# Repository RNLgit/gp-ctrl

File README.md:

# gp-ctrl
general purpose control board

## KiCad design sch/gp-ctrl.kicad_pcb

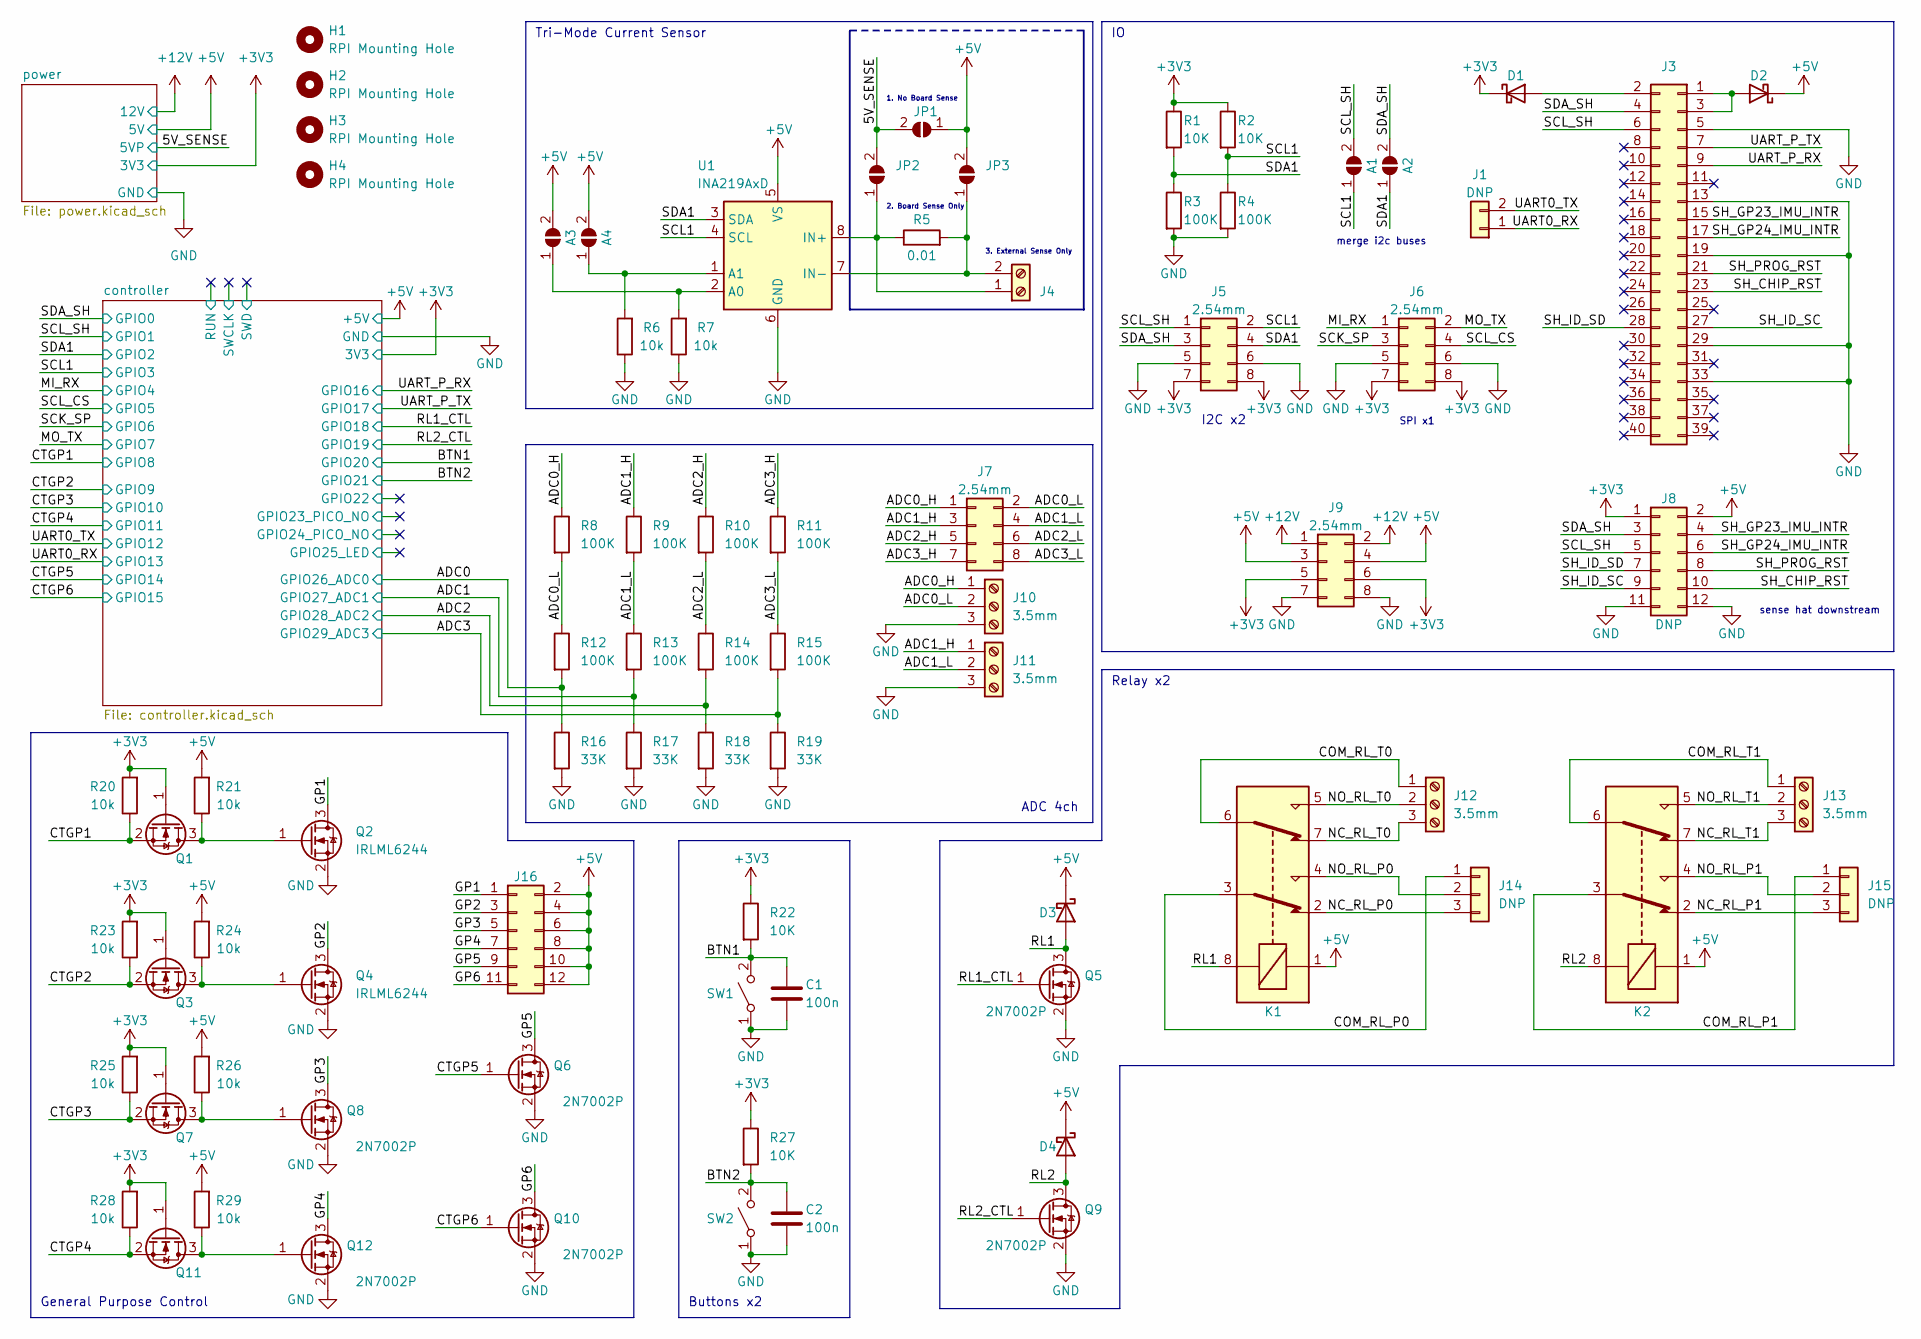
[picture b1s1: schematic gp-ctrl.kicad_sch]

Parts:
A1, A2, A3, A4: SolderJumper_2_Open; SolderJumper-2_P1.3mm_Open_TrianglePad1.0x1.5mm
C1, C2: 100n; R_0402_1005Metric_Pad0.72x0.64mm_HandSolder; LCSC C1525
D1, D2: SS34; D_SMA; LCSC C8678
D3, D4: B5819W SL; D_SOD-123; LCSC C8598
H1, H2, H3, H4: RPI Mounting Hole; MountingHole_3.2mm_M3_Pad
J1: DNP; PinHeader_1x02_P2.54mm_Vertical
J3: Conn_02x20_Odd_Even; Samtec_HLE-120-02-xxx-DV-BE_2x20_P2.54mm_Horizontal; LCSC C3975165
J4: Screw_Terminal_3.5mm; TerminalBlock_4Ucon_1x02_P3.50mm_Horizontal; LCSC C466970
J5, J6, J7, J9: 2.54mm; PinHeader_2x04_P2.54mm_Vertical; LCSC C225519
J8: DNP; PinHeader_2x06_P2.54mm_Vertical
J10, J11, J12, J13: 3.5mm; TerminalBlock_4Ucon_1x03_P3.50mm_Horizontal; LCSC C695630
J14, J15: DNP; PinHeader_1x03_P2.54mm_Vertical_SMD_Pin1Left
J16: Conn_02x06_Odd_Even; PinHeader_2x06_P2.54mm_Vertical; LCSC C225521
JP1, JP2, JP3: SolderJumper_2_Open; power_jumper
K1, K2: Relay_DPDT_Panasonic_AGQ200A4H; LCSC C490150
Q1, Q3, Q5, Q6, Q7, Q8, Q9, Q10, Q11, Q12: 2N7002P; SOT-23; LCSC C8545
Q2, Q4: IRLML6244; SOT-23; LCSC C143946
R1, R2, R22, R27: 10K; R_0603_1608Metric_Pad0.98x0.95mm_HandSolder; LCSC C25804
R3, R4, R8, R9, R10, R11, R12, R13, R14, R15: 100K; R_0603_1608Metric_Pad0.98x0.95mm_HandSolder; LCSC C25803
R5: 0.01; R_1210_3225Metric_Pad1.30x2.65mm_HandSolder; LCSC C473495
R6, R7, R20, R21, R23, R24, R25, R26, R28, R29: 10k; R_0402_1005Metric_Pad0.72x0.64mm_HandSolder; LCSC C25086
R16, R17, R18, R19: 33K; R_0603_1608Metric_Pad0.98x0.95mm_HandSolder; LCSC C4216
SW1, SW2: C2689642; SW_SPST_CK_PTS636_SP43_SMTR; LCSC C2689642
U1: INA219AxD; SOIC-8_3.9x4.9mm_P1.27mm; LCSC C138706

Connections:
+3V3: D1.1 (K), J5.7, J5.8, J6.7, J6.8, J8.1, J9.5, J9.6, Q1.1 (G), Q3.1 (G), Q7.1 (G), Q11.1 (G), R1.1, R2.1, R20.2, R22.1, R23.2, R25.2, R27.1, R28.2; also elsewhere on the board
+5V: A3.2 (B), A4.2 (B), D2.1 (K), D3.1 (K), D4.1 (K), J8.2, J9.3, J9.4, J16.2, J16.4, J16.6, J16.8, J16.10, J16.12, JP1.1 (A), JP3.2 (B), K1.1, K2.1, R21.2, R24.2, R26.2, R29.2, U1.5 (VS); also elsewhere on the board
+5VP: JP1.2 (B), JP2.2 (B); also elsewhere on the board
+12V: J9.1, J9.2; also elsewhere on the board
/ADC0: R12.2, R16.1; also elsewhere on the board
/ADC0_H: J7.1, J10.1, R8.1
/ADC0_L: J7.2, J10.2, R8.2, R12.1
/ADC1: R13.2, R17.1; also elsewhere on the board
/ADC1_H: J7.3, J11.1, R9.1
/ADC1_L: J7.4, J11.2, R9.2, R13.1
/ADC2: R14.2, R18.1; also elsewhere on the board
/ADC2_H: J7.5, R10.1
/ADC2_L: J7.6, R10.2, R14.1
/ADC3: R15.2, R19.1; also elsewhere on the board
/ADC3_H: J7.7, R11.1
/ADC3_L: J7.8, R11.2, R15.1
/BTN1: C1.1, R22.2, SW1.2 (B); also elsewhere on the board
/BTN2: C2.1, R27.2, SW2.2 (B); also elsewhere on the board
/COM_RL_P0: J14.1, K1.3
/COM_RL_P1: J15.1, K2.3
/COM_RL_T0: J12.1, K1.6
/COM_RL_T1: J13.1, K2.6
/CTGP1: Q1.2 (S), R20.1; also elsewhere on the board
/CTGP2: Q3.2 (S), R23.1; also elsewhere on the board
/CTGP3: Q7.2 (S), R25.1; also elsewhere on the board
/CTGP4: Q11.2 (S), R28.1; also elsewhere on the board
/CTGP5: Q6.1 (G); also elsewhere on the board
/CTGP6: Q10.1 (G); also elsewhere on the board
/GP1: J16.1, Q2.3 (D)
/GP2: J16.3, Q4.3 (D)
/GP3: J16.5, Q8.3 (D)
/GP4: J16.7, Q12.3 (D)
/GP5: J16.9, Q6.3 (D)
/GP6: J16.11, Q10.3 (D)
/MI_RX: J6.1; also elsewhere on the board
/MO_TX: J6.2; also elsewhere on the board
/NC_RL_P0: J14.3, K1.2
/NC_RL_P1: J15.3, K2.2
/NC_RL_T0: J12.3, K1.7
/NC_RL_T1: J13.3, K2.7
/NO_RL_P0: J14.2, K1.4
/NO_RL_P1: J15.2, K2.4
/NO_RL_T0: J12.2, K1.5
/NO_RL_T1: J13.2, K2.5
/RL1: D3.2 (A), K1.8, Q5.3 (D)
/RL1_CTL: Q5.1 (G); also elsewhere on the board
/RL2: D4.2 (A), K2.8, Q9.3 (D)
/RL2_CTL: Q9.1 (G); also elsewhere on the board
/SCK_SP: J6.3; also elsewhere on the board
/SCL1: A1.1 (A), J5.2, R2.2, R4.1, U1.4 (SCL); also elsewhere on the board
/SCL_CS: J6.4; also elsewhere on the board
/SCL_SH: A1.2 (B), J3.6, J5.1, J8.5; also elsewhere on the board
/SDA1: A2.1 (A), J5.4, R1.2, R3.1, U1.3 (SDA); also elsewhere on the board
/SDA_SH: A2.2 (B), J3.4, J5.3, J8.3; also elsewhere on the board
/SH_CHIP_RST: J3.23, J8.10
/SH_GP23_IMU_INTR: J3.15, J8.4
/SH_GP24_IMU_INTR: J3.17, J8.6
/SH_ID_SC: J3.27, J8.9
/SH_ID_SD: J3.28, J8.7
/SH_PROG_RST: J3.21, J8.8
/UART0_RX: J1.1; also elsewhere on the board
/UART0_TX: J1.2; also elsewhere on the board
/UART_P_RX: J3.9; also elsewhere on the board
/UART_P_TX: J3.7; also elsewhere on the board
GND: C1.2, C2.2, J3.5, J3.13, J3.19, J3.29, J3.33, J5.5, J5.6, J6.5, J6.6, J8.11, J8.12, J9.7, J9.8, J10.3, J11.3, Q2.2 (S), Q4.2 (S), Q5.2 (S), Q6.2 (S), Q8.2 (S), Q9.2 (S), Q10.2 (S), Q12.2 (S), R3.2, R4.2, R6.1, R7.1, R16.2, R17.2, R18.2, R19.2, SW1.1 (A), SW2.1 (A), U1.6 (GND); also elsewhere on the board
unnamed: A3.1 (A), R7.2, U1.2 (A0)
unnamed: A4.1 (A), R6.2, U1.1 (A1)
unnamed: D2.2 (A), J3.1, J3.3
unnamed: D1.2 (A), J3.2
unnamed: J4.1, JP2.1 (A), R5.1, U1.8 (IN+)
unnamed: J4.2, JP3.1 (A), R5.2, U1.7 (IN-)
unnamed: Q1.3 (D), Q2.1 (G), R21.1
unnamed: Q3.3 (D), Q4.1 (G), R24.1
unnamed: Q7.3 (D), Q8.1 (G), R26.1
unnamed: Q11.3 (D), Q12.1 (G), R29.1

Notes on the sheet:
Buttons x2
3. External Sense Only
2. Board Sense Only
General Purpose Control
SPI x1
ADC 4ch
sense hat downstream
Relay x2
merge i2c buses
Tri-Mode Current Sensor
1. No Board Sense
I2C x2

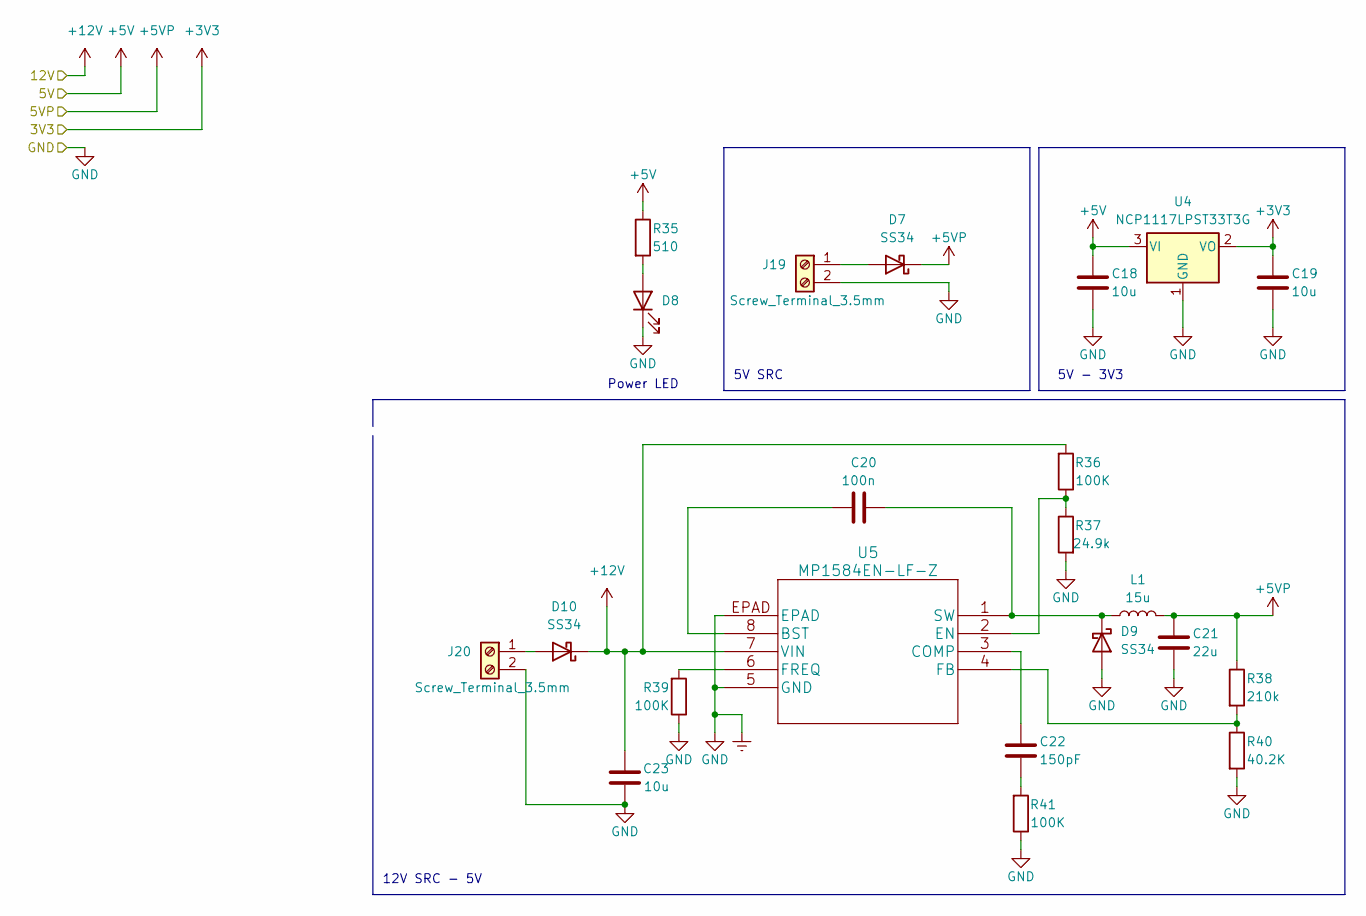
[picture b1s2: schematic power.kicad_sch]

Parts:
C18, C19: 10u; C_0603_1608Metric_Pad1.08x0.95mm_HandSolder; LCSC C96446
C20: 100n; R_0402_1005Metric_Pad0.72x0.64mm_HandSolder; LCSC C1525
C21: 22u; C_1206_3216Metric_Pad1.33x1.80mm_HandSolder; LCSC C12891
C22: 150pF; R_0402_1005Metric_Pad0.72x0.64mm_HandSolder; LCSC C1527
C23: 10u; C_0805_2012Metric_Pad1.18x1.45mm_HandSolder; LCSC C440198
D7, D9, D10: SS34; D_SMA; LCSC C8678
D8: 19-217/GHC-YR1S2/3T; D_0603_1608Metric_Pad1.05x0.95mm_HandSolder; LCSC C72043
J19, J20: Screw_Terminal_3.5mm; TerminalBlock_4Ucon_1x02_P3.50mm_Horizontal; LCSC C466970
L1: 15u; L_12x12mm_H6mm; LCSC C169384
R35: 510; R_0402_1005Metric_Pad0.72x0.64mm_HandSolder; LCSC C25123
R36, R39, R41: 100K; R_0402_1005Metric_Pad0.72x0.64mm_HandSolder; LCSC C25741
R37: 24.9k; R_0402_1005Metric_Pad0.72x0.64mm_HandSolder; LCSC C226371
R38: 210k; R_0402_1005Metric_Pad0.72x0.64mm_HandSolder; LCSC C58827
R40: 40.2K; R_0402_1005Metric_Pad0.72x0.64mm_HandSolder; LCSC C137983
U4: NCP1117LPST33T3G; SOT-223-3_TabPin2; LCSC C146799
U5: MP1584EN-LF-Z; LCSC C15051

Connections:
+3V3: C19.1, U4.2 (VO); also elsewhere on the board
+5V: C18.1, R35.1, U4.3 (VI); also elsewhere on the board
+5VP: C21.1, D7.1 (K), L1.2, R38.1; also elsewhere on the board
+12V: C23.1, D10.1 (K), R36.2, U5.7 (VIN); also elsewhere on the board
GND: C18.2, C19.2, C21.2, C23.2, D8.1 (K), D9.2 (A), J19.2, J20.2, R37.2, R39.1, R40.2, R41.1, U4.1 (GND), U5.5 (GND), U5.EPAD; also elsewhere on the board
unnamed: C20.1, D9.1 (K), L1.1, U5.1 (SW)
unnamed: C20.2, U5.8 (BST)
unnamed: C22.1, U5.3 (COMP)
unnamed: C22.2, R41.2
unnamed: D7.2 (A), J19.1
unnamed: D8.2 (A), R35.2
unnamed: D10.2 (A), J20.1
unnamed: R36.1, R37.1, U5.2 (EN)
unnamed: R38.2, R40.1, U5.4 (FB)
unnamed: R39.2, U5.6 (FREQ)

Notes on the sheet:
5V - 3V3
12V SRC - 5V
Power LED
5V SRC

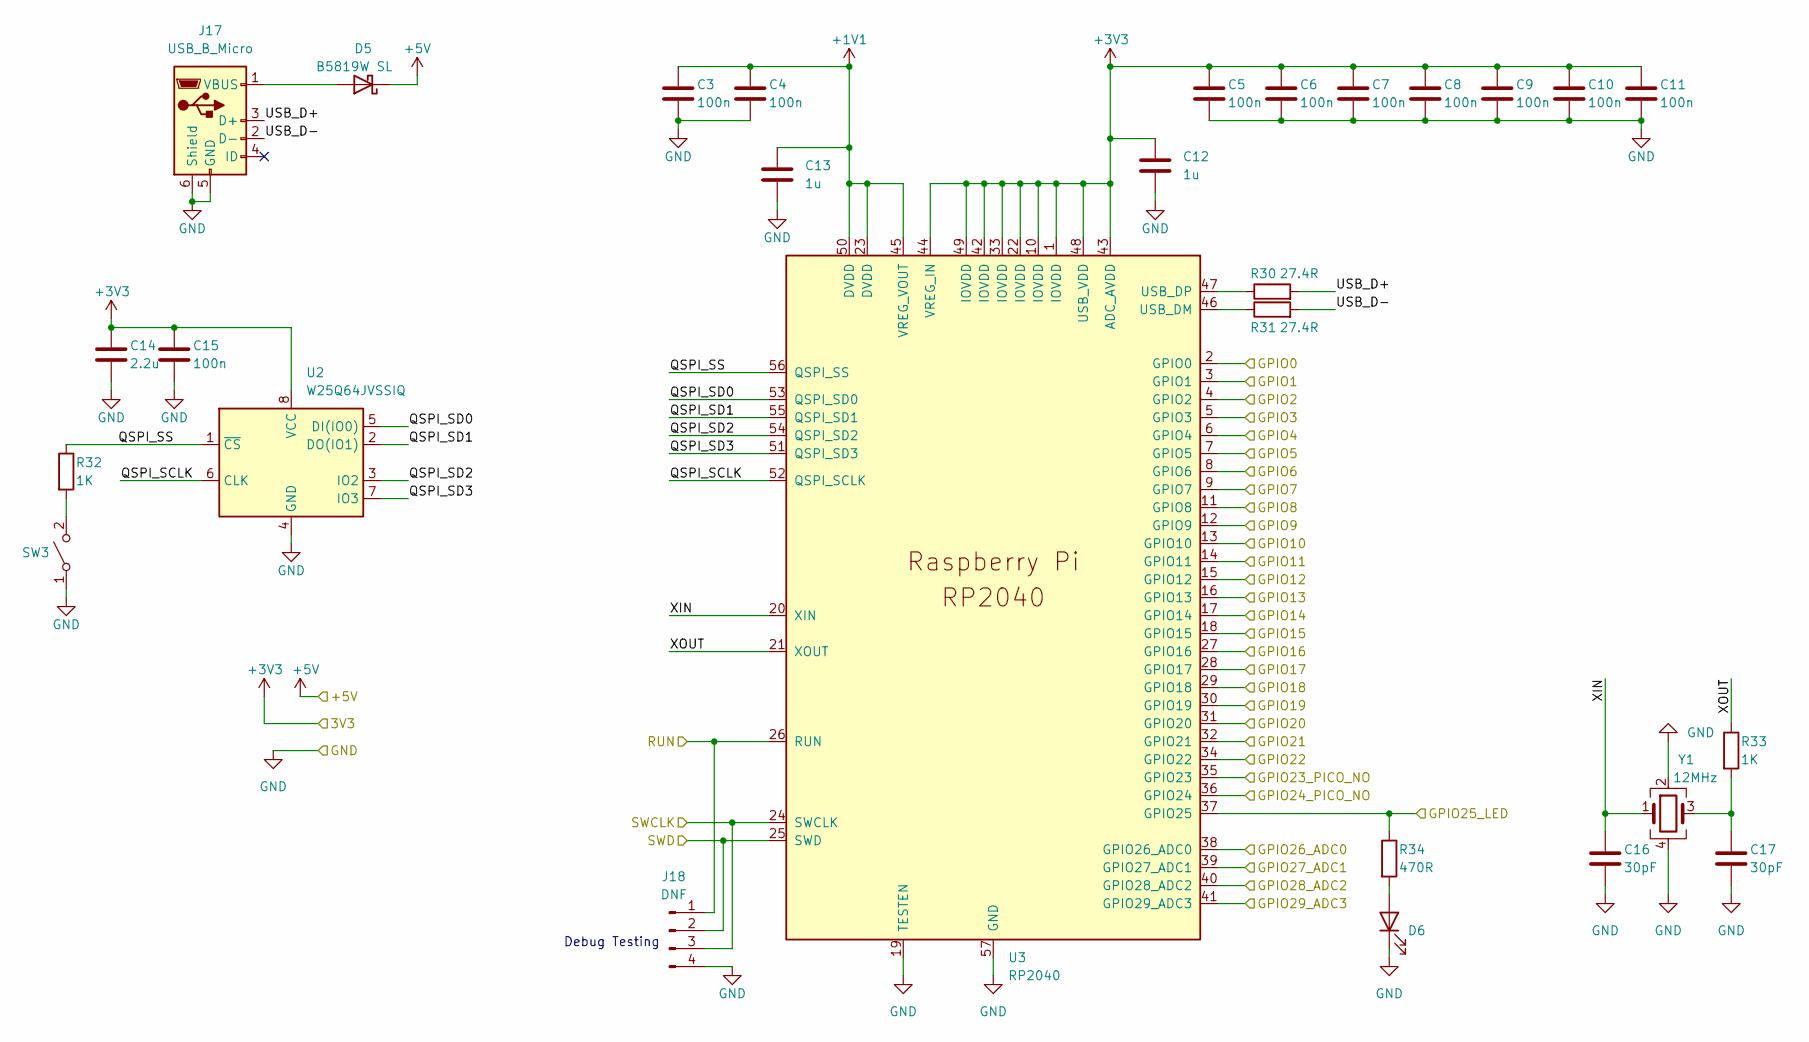
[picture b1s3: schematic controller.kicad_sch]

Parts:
C3, C4, C5, C6, C7, C8, C9, C10, C11: 100n; R_0402_1005Metric_Pad0.72x0.64mm_HandSolder; LCSC C1525
C12, C13: 1u; R_0402_1005Metric_Pad0.72x0.64mm_HandSolder; LCSC C52923
C14: 2.2u; L_0402_1005Metric_Pad0.77x0.64mm_HandSolder; LCSC C12530
C15: 100n; L_0402_1005Metric_Pad0.77x0.64mm_HandSolder; LCSC C1525
C16, C17: 30pF; C_0402_1005Metric_Pad0.74x0.62mm_HandSolder; LCSC C1570
D5: B5819W SL; D_SOD-123; LCSC C8598
D6: 19-217/GHC-YR1S2/3T; D_0603_1608Metric_Pad1.05x0.95mm_HandSolder; LCSC C72043
J17: USB_B_Micro; USB_Micro-B_Molex-105017-0001; LCSC C10418
J18: DNF; PinHeader_1x04_P1.00mm_Vertical_SMD_Pin1Left
R30, R31: 27.4R; R_0402_1005Metric_Pad0.72x0.64mm_HandSolder; LCSC C31439
R32, R33: 1K; L_0402_1005Metric_Pad0.77x0.64mm_HandSolder; LCSC C11702
R34: 470R; R_0402_1005Metric_Pad0.72x0.64mm_HandSolder; LCSC C25117
SW3: C2689642; SW_SPST_CK_PTS636_SP43_SMTR; LCSC C2689642
U2: W25Q64JVSSIQ; SOIC-8_5.23x5.23mm_P1.27mm; LCSC C83140
U3: RP2040; RP2040-QFN-56; LCSC C2040
Y1: 12MHz; Crystal_SMD_3225-4Pin_3.2x2.5mm; LCSC C9002

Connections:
+1V1: C3.1, C4.1, C13.1, U3.23 (DVDD), U3.45 (VREG_VOUT), U3.50 (DVDD)
+3V3: C5.1, C6.1, C7.1, C8.1, C9.1, C10.1, C11.1, C12.1, C14.1, C15.1, U2.8 (VCC), U3.1 (IOVDD), U3.10 (IOVDD), U3.22 (IOVDD), U3.33 (IOVDD), U3.42 (IOVDD), U3.43 (ADC_AVDD), U3.44 (VREG_IN), U3.48 (USB_VDD), U3.49 (IOVDD); also elsewhere on the board
+5V: D5.1 (K); also elsewhere on the board
/ADC0: U3.38 (GPIO26_ADC0); also elsewhere on the board
/ADC1: U3.39 (GPIO27_ADC1); also elsewhere on the board
/ADC2: U3.40 (GPIO28_ADC2); also elsewhere on the board
/ADC3: U3.41 (GPIO29_ADC3); also elsewhere on the board
/BTN1: U3.31 (GPIO20); also elsewhere on the board
/BTN2: U3.32 (GPIO21); also elsewhere on the board
/CTGP1: U3.11 (GPIO8); also elsewhere on the board
/CTGP2: U3.12 (GPIO9); also elsewhere on the board
/CTGP3: U3.13 (GPIO10); also elsewhere on the board
/CTGP4: U3.14 (GPIO11); also elsewhere on the board
/CTGP5: U3.17 (GPIO14); also elsewhere on the board
/CTGP6: U3.18 (GPIO15); also elsewhere on the board
/MI_RX: U3.6 (GPIO4); also elsewhere on the board
/MO_TX: U3.9 (GPIO7); also elsewhere on the board
/RL1_CTL: U3.29 (GPIO18); also elsewhere on the board
/RL2_CTL: U3.30 (GPIO19); also elsewhere on the board
/SCK_SP: U3.8 (GPIO6); also elsewhere on the board
/SCL1: U3.5 (GPIO3); also elsewhere on the board
/SCL_CS: U3.7 (GPIO5); also elsewhere on the board
/SCL_SH: U3.3 (GPIO1); also elsewhere on the board
/SDA1: U3.4 (GPIO2); also elsewhere on the board
/SDA_SH: U3.2 (GPIO0); also elsewhere on the board
/UART0_RX: U3.16 (GPIO13); also elsewhere on the board
/UART0_TX: U3.15 (GPIO12); also elsewhere on the board
/UART_P_RX: U3.27 (GPIO16); also elsewhere on the board
/UART_P_TX: U3.28 (GPIO17); also elsewhere on the board
/controller/GPIO22: U3.34 (GPIO22)
/controller/GPIO23_PICO_NO: U3.35 (GPIO23)
/controller/GPIO24_PICO_NO: U3.36 (GPIO24)
/controller/GPIO25_LED: R34.1, U3.37 (GPIO25)
/controller/QSPI_SCLK: U2.6 (CLK), U3.52 (QSPI_SCLK)
/controller/QSPI_SD0: U2.5 (DI(IO0)), U3.53 (QSPI_SD0)
/controller/QSPI_SD1: U2.2 (DO(IO1)), U3.55 (QSPI_SD1)
/controller/QSPI_SD2: U2.3 (IO2), U3.54 (QSPI_SD2)
/controller/QSPI_SD3: U2.7 (IO3), U3.51 (QSPI_SD3)
/controller/QSPI_SS: R32.1, U2.1 (~CS), U3.56 (QSPI_SS)
/controller/RUN: J18.1, U3.26 (RUN)
/controller/SWCLK: J18.3, U3.24 (SWCLK)
/controller/SWD: J18.2, U3.25 (SWD)
/controller/USB_D+: J17.3 (D+), R30.2
/controller/USB_D-: J17.2 (D-), R31.2
/controller/XIN: C16.1, U3.20 (XIN), Y1.1
/controller/XOUT: R33.1, U3.21 (XOUT)
GND: C3.2, C4.2, C5.2, C6.2, C7.2, C8.2, C9.2, C10.2, C11.2, C12.2, C13.2, C14.2, C15.2, C16.2, C17.2, D6.1 (K), J17.5 (GND), J17.6 (Shield), J18.4, SW3.1 (A), U2.4 (GND), U3.19 (TESTEN), U3.57 (GND), Y1.2, Y1.4; also elsewhere on the board
unnamed: C17.1, R33.2, Y1.3
unnamed: D5.2 (A), J17.1 (VBUS)
unnamed: D6.2 (A), R34.2
unnamed: R30.1, U3.47 (USB_DP)
unnamed: R31.1, U3.46 (USB_DM)
unnamed: R32.2, SW3.2 (B)

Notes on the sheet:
Debug Testing

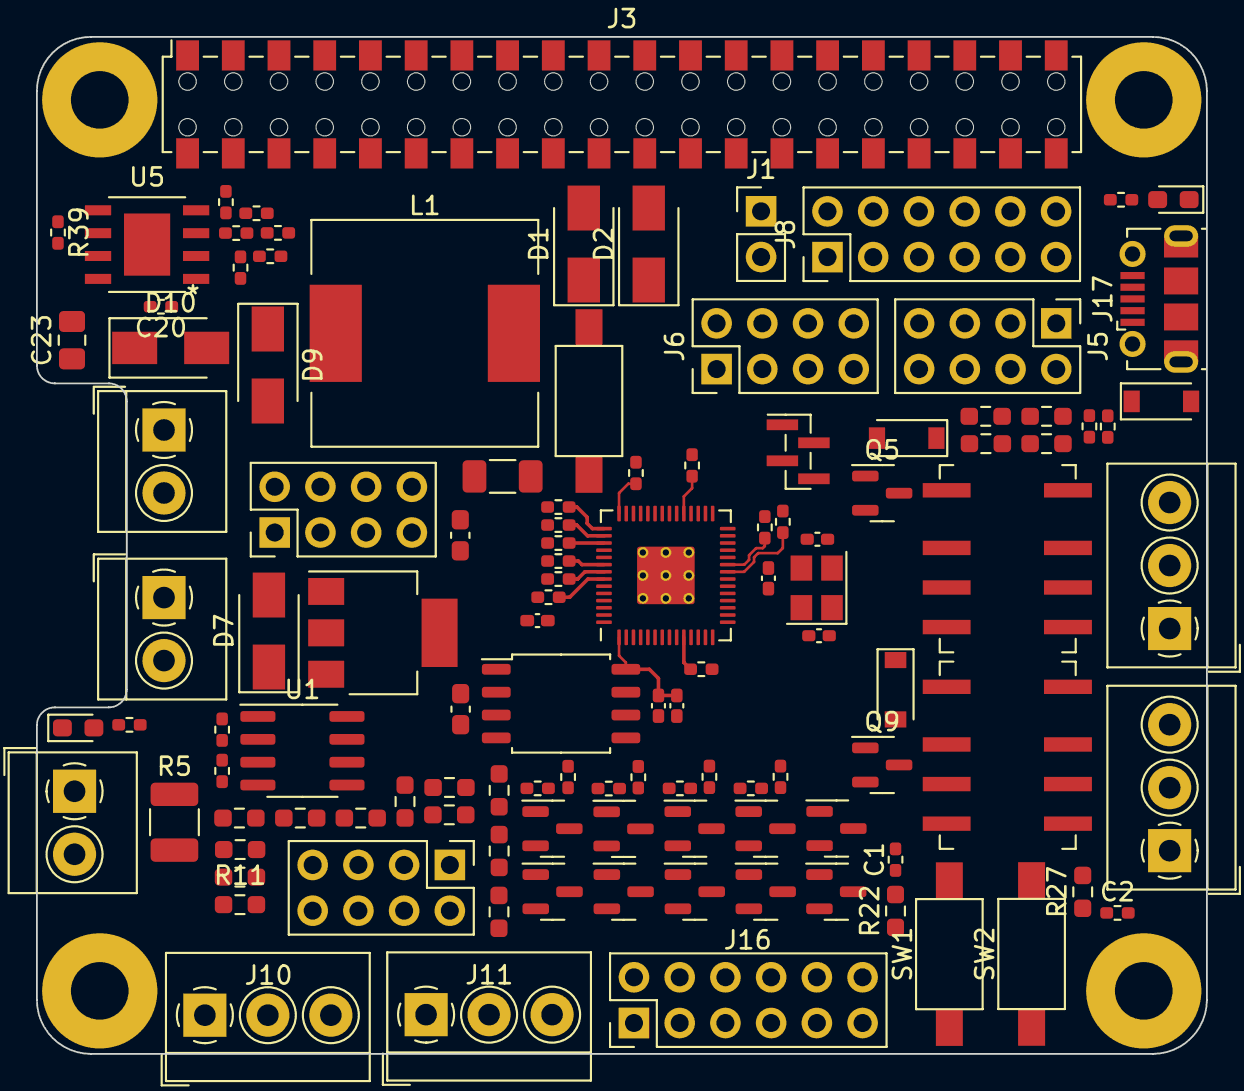
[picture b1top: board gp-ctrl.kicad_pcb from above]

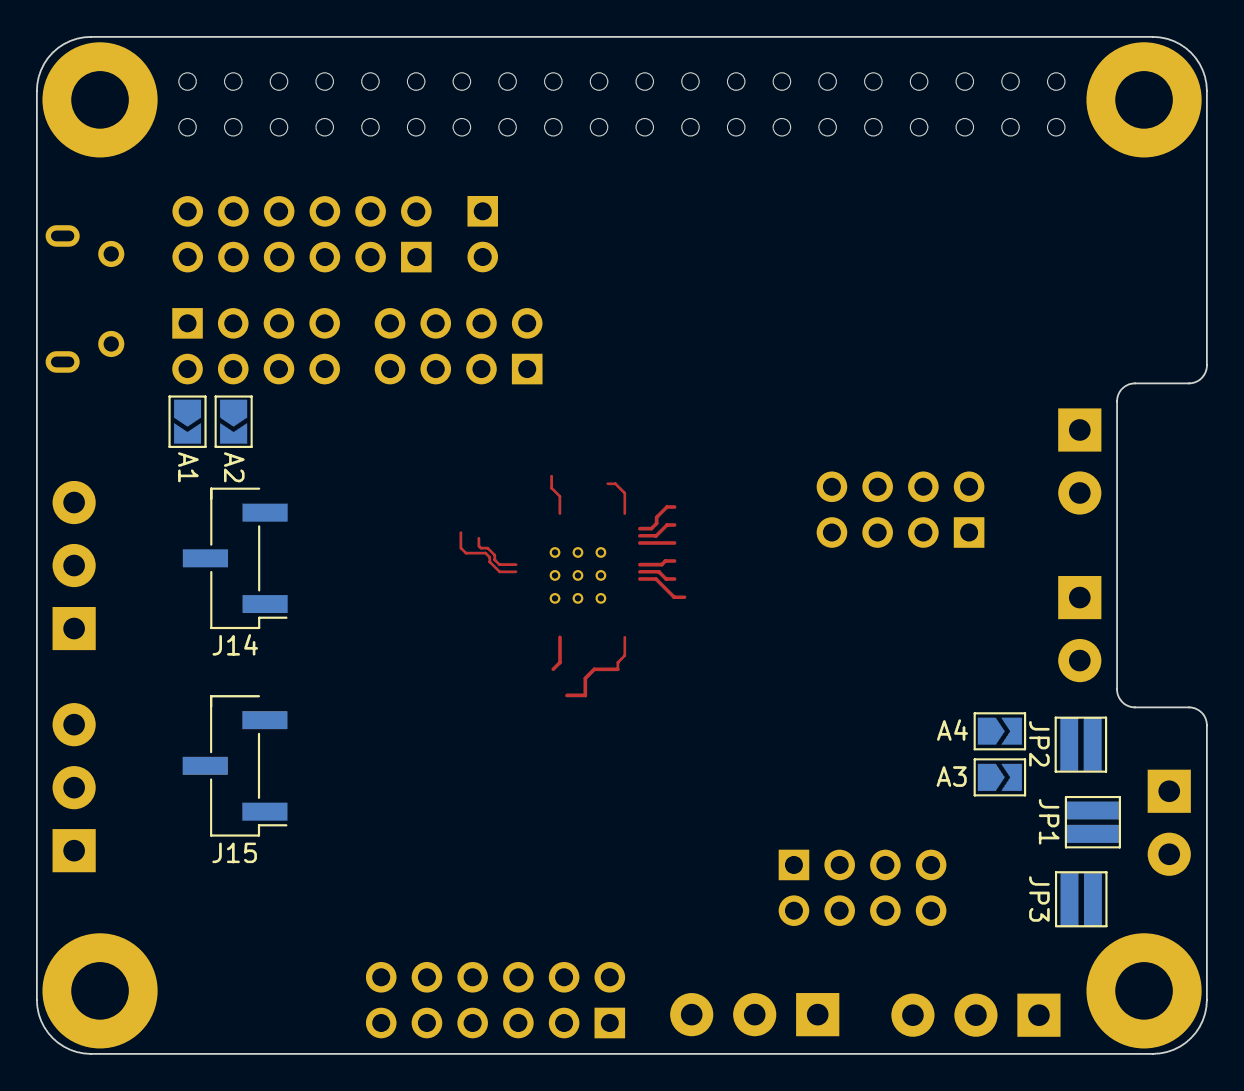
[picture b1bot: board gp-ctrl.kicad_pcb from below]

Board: 2 copper layers, 65.0 x 56.5 mm, 128 parts (9 on the bottom side), 106 nets.

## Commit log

2022-11-30 init
2022-12-01 more components
2022-12-02 removed arch .bkp file
2022-12-02 updated downstream to sense hat connector
2022-12-02 sch update
2022-12-05 adc added
2022-12-08 sch and pcb layout update
2022-12-11 updated pcb
